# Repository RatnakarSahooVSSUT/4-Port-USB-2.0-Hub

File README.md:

<h1 align="center">4-Port USB 2.0 Hub PCB</h1>

<p align="center">
  <strong>From a simple weekend idea to a custom hardware design.</strong>
  <br>
  A USB hub PCB designed in KiCad featuring USB-C and USB-A connectivity.
</p>

---

## Overview

What started as a search for a USB hub to buy turned into a weekend PCB design project.

Instead of purchasing one, I decided to explore the hardware design process myself — studying datasheets, understanding the hub controller and its supporting circuitry, designing the schematic, and routing a custom PCB.

The result is a **4-port USB 2.0 hub design** with a combination of USB-C and USB-A interfaces.

## Hardware Features

| Feature | Specification |
|---|---|
| Hub Controller | GL852G |
| USB Standard | USB 2.0 |
| Upstream Interface | 1 × USB-C |
| Downstream Interfaces | 2 × USB-C + 2 × USB-A |
| Design Tool | KiCad |
| PCB Design | Custom schematic and PCB layout |
| Signal Routing | USB D+ and D− differential pairs |

## PCB Design

### 3D Visualization

### PCB Layout

### Schematic

## Design and Development

The project involves:

- Studying the GL852G datasheet and understanding the controller's pin configuration.
- Designing the schematic and supporting circuitry.
- Selecting components and assigning footprints.
- Developing the PCB layout in KiCad.
- Routing USB D+ and D− differential pairs with impedance considerations.
- Reviewing connector placement and mechanical dimensions.
- Preparing the design for electrical verification and manufacturing.

## Technology Stack

## Current Status

**PCB Design — In Progress**

The schematic and PCB layout have been developed, and the board has been visualized in KiCad's 3D viewer.

### Next Steps

- Complete electrical rule checks (ERC) and design rule checks (DRC).
- Verify connector footprints and component dimensions.
- Review power delivery, protection circuitry, and USB signal integrity.
- Finalize the PCB layout for manufacturing.
- Assemble and test the physical prototype.

## Repository Structure

```text
4-Port-USB-2.0-Hub/
├── Hardware/
│   ├── USB_HUB.kicad_pro
│   ├── USB_HUB.kicad_sch
│   └── USB_HUB.kicad_pcb
├── Images/
│   ├── PCB_3D_View.png
│   ├── PCB_3D_View_2.png
│   ├── PCB_Layout.png
│   └── PCB_Schematic.png
├── Libraries/
│   ├── GL852G/
│   ├── TPS2042BDR/
│   ├── TPS2552DBVR/
│   └── TPS2553DBVR/
├── Documentation/
├── .gitignore
└── README.md

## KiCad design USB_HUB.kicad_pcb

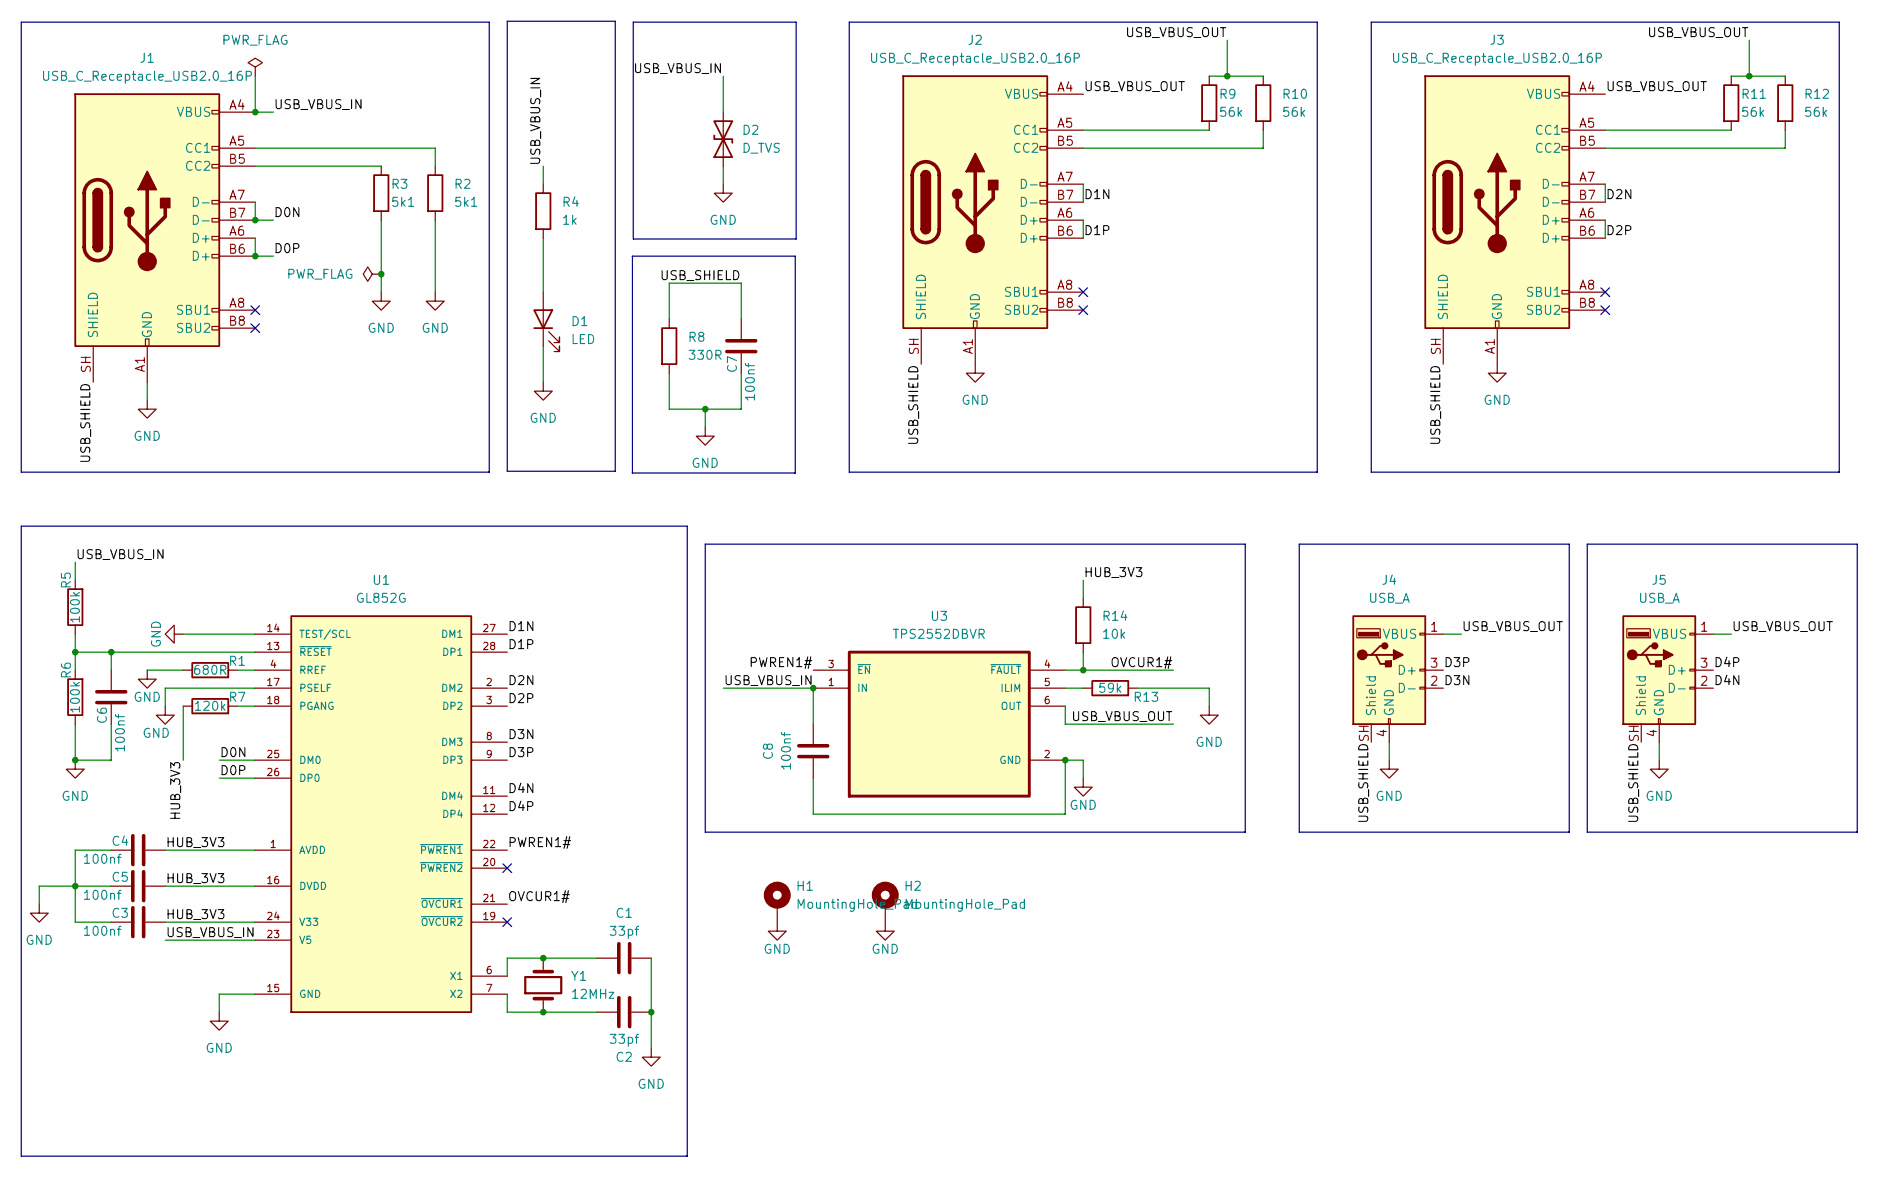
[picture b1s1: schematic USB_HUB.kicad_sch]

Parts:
C1, C2: 33pf; C_0603_1608Metric_Pad1.08x0.95mm_HandSolder
C3, C4, C5, C6, C7, C8: 100nf; C_0603_1608Metric_Pad1.08x0.95mm_HandSolder
D1: LED; LED_0603_1608Metric_Pad1.05x0.95mm_HandSolder
D2: D_TVS; D_SMB
H1, H2: MountingHole_Pad; MountingHole_2.2mm_M2_Pad_Via
J1, J2, J3: USB_C_Receptacle_USB2.0_16P; USB_C_Receptacle_GCT_USB4105-xx-A_16P_TopMnt_Horizontal
J4, J5: USB_A; USB_A_TE_292303-7_Horizontal
R1: 680R; R_0603_1608Metric_Pad0.98x0.95mm_HandSolder
R2, R3: 5k1; R_0603_1608Metric_Pad0.98x0.95mm_HandSolder
R4: 1k; R_0603_1608Metric_Pad0.98x0.95mm_HandSolder
R5, R6: 100k; R_0603_1608Metric_Pad0.98x0.95mm_HandSolder
R7: 120k; R_0603_1608Metric_Pad0.98x0.95mm_HandSolder
R8: 330R; R_0603_1608Metric_Pad0.98x0.95mm_HandSolder
R9, R10, R11, R12: 56k; R_0603_1608Metric_Pad0.98x0.95mm_HandSolder
R13: 59k; R_0603_1608Metric_Pad0.98x0.95mm_HandSolder
R14: 10k; R_0603_1608Metric_Pad0.98x0.95mm_HandSolder
U1: GL852G; SSOP28
U3: TPS2552DBVR; SOT95P280X145-6N
Y1: 12MHz; Crystal_SMD_5032-2Pin_5.0x3.2mm

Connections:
/D0N: J1.A7 (D-), J1.B7 (D-), U1.25 (DM0)
/D0P: J1.A6 (D+), J1.B6 (D+), U1.26 (DP0)
/D1N: J2.A7 (D-), J2.B7 (D-), U1.27 (DM1)
/D1P: J2.A6 (D+), J2.B6 (D+), U1.28 (DP1)
/D2N: J3.A7 (D-), J3.B7 (D-), U1.2 (DM2)
/D2P: J3.A6 (D+), J3.B6 (D+), U1.3 (DP2)
/D3N: J4.2 (D-), U1.8 (DM3)
/D3P: J4.3 (D+), U1.9 (DP3)
/D4N: J5.2 (D-), U1.11 (DM4)
/D4P: J5.3 (D+), U1.12 (DP4)
/HUB_3V3: C3.2, C4.2, C5.2, R7.1, R14.1, U1.1 (AVDD), U1.5 (AVDD), U1.10 (AVDD), U1.16 (DVDD), U1.24 (V33)
/OVCUR1#: R14.2, U1.21 (~OVCUR1), U3.4 (~FAULT)
/PWREN1#: U1.22 (~PWREN1), U3.3 (~EN)
/USB_SHIELD: C7.2, J1.SH (SHIELD), J2.SH (SHIELD), J3.SH (SHIELD), J4.SH (Shield), J5.SH (Shield), R8.1
/USB_VBUS_IN: C8.2, D2.2 (A2), J1.A4 (VBUS), J1.A9 (VBUS), J1.B4 (VBUS), J1.B9 (VBUS), R4.1, R5.2, U1.23 (V5), U3.1 (IN)
/USB_VBUS_OUT: J2.A4 (VBUS), J2.A9 (VBUS), J2.B4 (VBUS), J2.B9 (VBUS), J3.A4 (VBUS), J3.A9 (VBUS), J3.B4 (VBUS), J3.B9 (VBUS), J4.1 (VBUS), J5.1 (VBUS), R9.1, R10.1, R11.1, R12.1, U3.6 (OUT)
GND: C1.2, C2.2, C3.1, C4.1, C5.1, C6.1, C7.1, C8.1, D1.1 (K), D2.1 (A1), H1.1 (1_1), H2.1 (1_1), J1.A1 (GND), J1.A12 (GND), J1.B1 (GND), J1.B12 (GND), J2.A1 (GND), J2.A12 (GND), J2.B1 (GND), J2.B12 (GND), J3.A1 (GND), J3.A12 (GND), J3.B1 (GND), J3.B12 (GND), J4.4 (GND), J5.4 (GND), R1.1, R2.2, R3.2, R6.1, R8.2, R13.2, U1.14 (TEST/SCL), U1.15 (GND), U1.17 (PSELF), U3.2 (GND)
unnamed: D1.2 (A), R4.2
unnamed: J1.A5 (CC1), R2.1
unnamed: J1.B5 (CC2), R3.1
unnamed: J2.A5 (CC1), R9.2
unnamed: J2.B5 (CC2), R10.2
unnamed: J3.A5 (CC1), R11.2
unnamed: J3.B5 (CC2), R12.2
unnamed: R7.2, U1.18 (PGANG)
unnamed: R1.2, U1.4 (RREF)
unnamed: C1.1, U1.6 (X1), Y1.2
unnamed: C2.1, U1.7 (X2), Y1.1
unnamed: C6.2, R5.1, R6.2, U1.13 (~RESET)
unnamed: R13.1, U3.5 (ILIM)

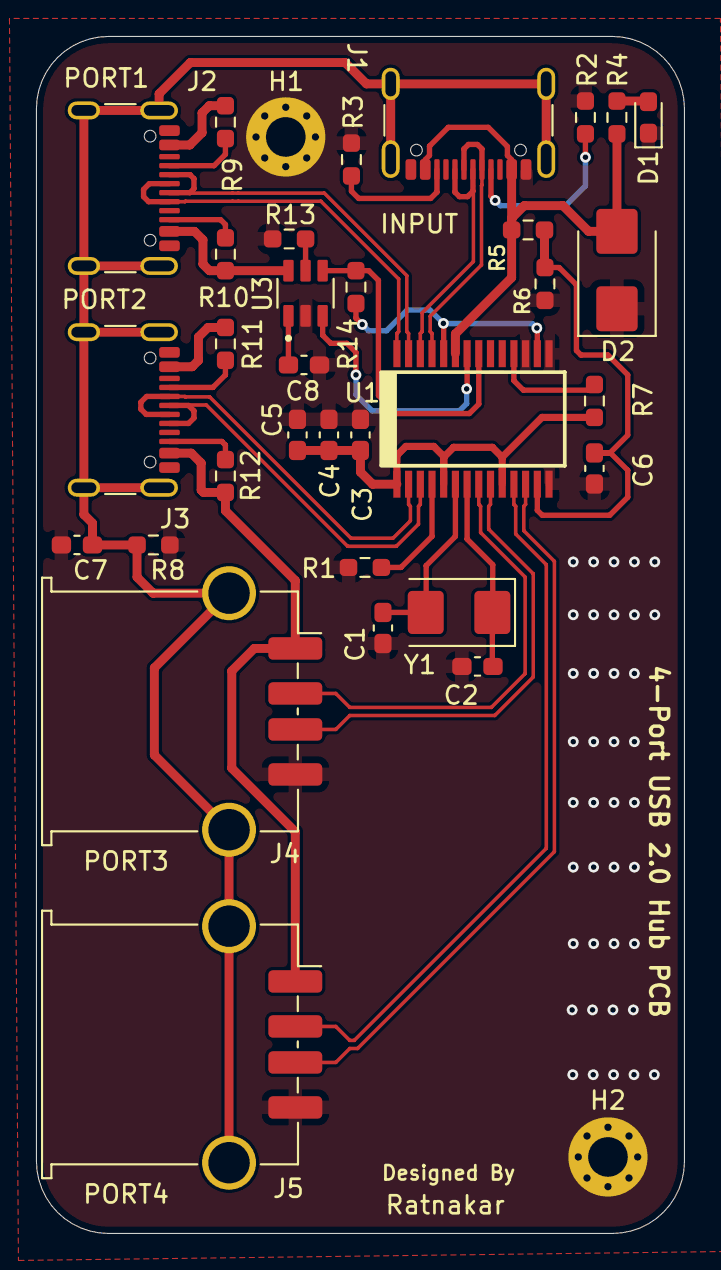
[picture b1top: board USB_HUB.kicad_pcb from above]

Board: 2 copper layers, 36.0 x 66.5 mm, 34 parts (0 on the bottom side), 30 nets.
